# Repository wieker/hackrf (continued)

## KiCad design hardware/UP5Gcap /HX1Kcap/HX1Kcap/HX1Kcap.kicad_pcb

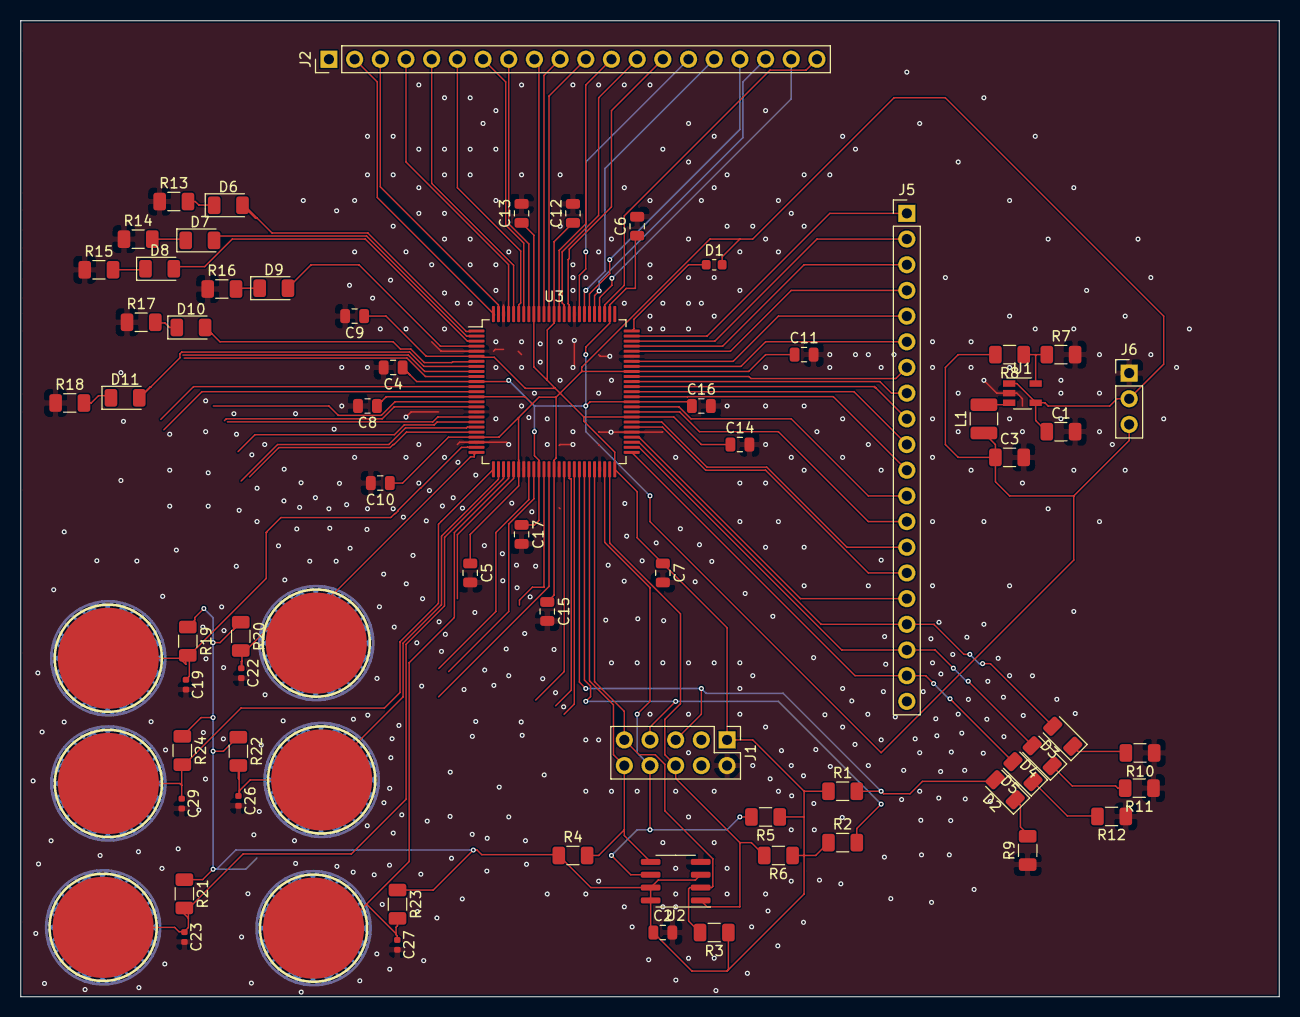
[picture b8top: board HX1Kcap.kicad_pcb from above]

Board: 2 copper layers, 124.5 x 96.5 mm, 72 parts (0 on the bottom side), 72 nets.

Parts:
C1: 4.7uF; C_1206_3216Metric
C2, C4, C5, C6, C7, C8, C9, C10, C11, C12, C13, C14, C15, C16, C17: 0.1uF; C_0805_2012Metric
C3: 10uF; C_1206_3216Metric
C18, C20, C21, C24, C25, C28: Button; CAPBUTTON
C19, C22, C23, C26, C27, C29: 100 pF; C_0402_1005Metric
D1: D; C_0603_1608Metric
D2, D3, D4, D5, D6, D7, D8, D9, D10, D11: LED; LED_1206_3216Metric
J1: Conn_02x05_Odd_Even; PinHeader_2x05_P2.54mm_Vertical
J2, J5: Conn_01x20_Male; PinHeader_1x20_P2.54mm_Vertical
J6: Conn_01x03_Male; PinHeader_1x03_P2.54mm_Vertical
L1: 2.2uH; L_1210_3225Metric
R1, R2, R3, R4, R5, R6: R; R_1206_3216Metric
R7, R8: 100kOhm; R_1206_3216Metric
R9, R10, R11, R12, R13, R14, R15, R16, R17, R18: 10kohm; R_1206_3216Metric
R19, R20, R21, R22, R23, R24: 100 kOhm; R_1206_3216Metric
U1: LTC3406ES5; TSOT-23-5
U2: AT25SF081-SSHD-X; SOIC-8_3.9x4.9mm_P1.27mm
U3: ICE40HX1K-VQ100(VQFP100); LQFP-100_14x14mm_P0.5mm

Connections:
+1V2: C3.1, C4.1, C6.1, C16.1, C17.1, J6.3, L1.1, R8.2, U3.11, U3.35, U3.61, U3.77
+3V3: C1.1, C2.1, C5.1, C7.1, C8.1, C9.1, C10.1, C11.1, C12.1, C13.1, C14.1, C15.1, D1.2, J1.1, J6.2, R1.1, R2.1, R3.1, R4.1, R5.1, R6.1, R19.1, R20.1, R21.1, R22.1, R23.1, R24.1, U1.1, U1.4, U2.3, U2.7, U2.8, U3.6, U3.14, U3.22, U3.31, U3.38, U3.50, U3.58, U3.67, U3.88, U3.92
CDONE: D2.2, J1.5, R1.2, U3.43
CRESET: J1.7, R2.2, U3.44
GND: C1.2, C2.2, C3.2, C4.2, C5.2, C6.2, C7.2, C8.2, C9.2, C10.2, C11.2, C12.2, C13.2, C14.2, C15.2, C16.2, C17.2, C18.2, C19.2, C20.2, C21.2, C22.2, C23.2, C24.2, C25.2, C26.2, C27.2, C28.2, C29.2, J1.2, J6.1, R7.2, R9.1, R10.1, R11.1, R12.1, R13.1, R14.1, R15.1, R16.1, R17.1, R18.1, U1.2, U2.4, U3.5, U3.17, U3.23, U3.32, U3.39, U3.47, U3.55, U3.70, U3.84, U3.98
IO1: D6.2, U3.1
IO2: D7.2, U3.2
IO3: D8.2, U3.3
IO4: D9.2, U3.4
IO7: D10.2, U3.7
IO8: D11.2, U3.8
IO24: C18.1, C19.1, R19.2, U3.24
IO25: C20.1, C22.1, R20.2, U3.25
IO26: C28.1, C29.1, R24.2, U3.26
IO27: C24.1, C26.1, R22.2, U3.27
IO28: C21.1, C23.1, R21.2, U3.28
IO29: C25.1, C27.1, R23.2, U3.29
IO51: D5.2, J5.19, U3.51
IO52: D4.2, J5.18, U3.52
IO53: D3.2, J5.17, U3.53
IO54: J5.16, U3.54
IO56: J5.15, U3.56
IO57: J5.14, U3.57
IO59: J5.13, U3.59
IO60: J5.12, U3.60
IO62: J5.11, U3.62
IO63: J5.10, U3.63
IO64: J5.9, U3.64
IO65: J5.8, U3.65
IO66: J5.7, U3.66
IO68: J5.6, U3.68
IO69: J5.5, U3.69
IO71: J5.4, U3.71
IO72: J5.3, U3.72
IO73: J5.2, U3.73
IO74: J5.1, U3.74
IO78: J2.20, U3.78
IO79: J2.19, U3.79
IO80: J2.18, U3.80
IO81: J2.17, U3.81
IO82: J2.16, U3.82
IO83: J2.15, U3.83
IO85: J2.14, U3.85
IO86: J2.13, U3.86
IO87: J2.12, U3.87
IO89: J2.11, U3.89
IO90: J2.10, U3.90
IO91: J2.9, U3.91
IO93: J2.8, U3.93
IO94: J2.7, U3.94
IO95: J2.6, U3.95
IO96: J2.5, U3.96
IO97: J2.4, U3.97
IO99: J2.3, U3.99
IO100: J2.2, U3.100
unnamed: D1.1, U3.75
unnamed: D2.1, R9.2
unnamed: D3.1, R10.2
unnamed: D4.1, R11.2
unnamed: D5.1, R12.2
unnamed: D6.1, R13.2
unnamed: D7.1, R14.2
unnamed: D8.1, R15.2
unnamed: D9.1, R16.2
unnamed: D10.1, R17.2
unnamed: D11.1, R18.2
unnamed: L1.2, U1.3
unnamed: R7.1, R8.1, U1.5
SPI_CS: J1.6, R6.2, U2.1, U3.49
SPI_IN: J1.9, R3.2, U2.2, U3.46
SPI_OUT: J1.10, R4.2, U2.5, U3.45
SPI_SCK: J1.8, R5.2, U2.6, U3.48
